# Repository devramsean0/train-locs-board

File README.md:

# train-locs-board
A LED train location board, meant to show the trains on platform at any station

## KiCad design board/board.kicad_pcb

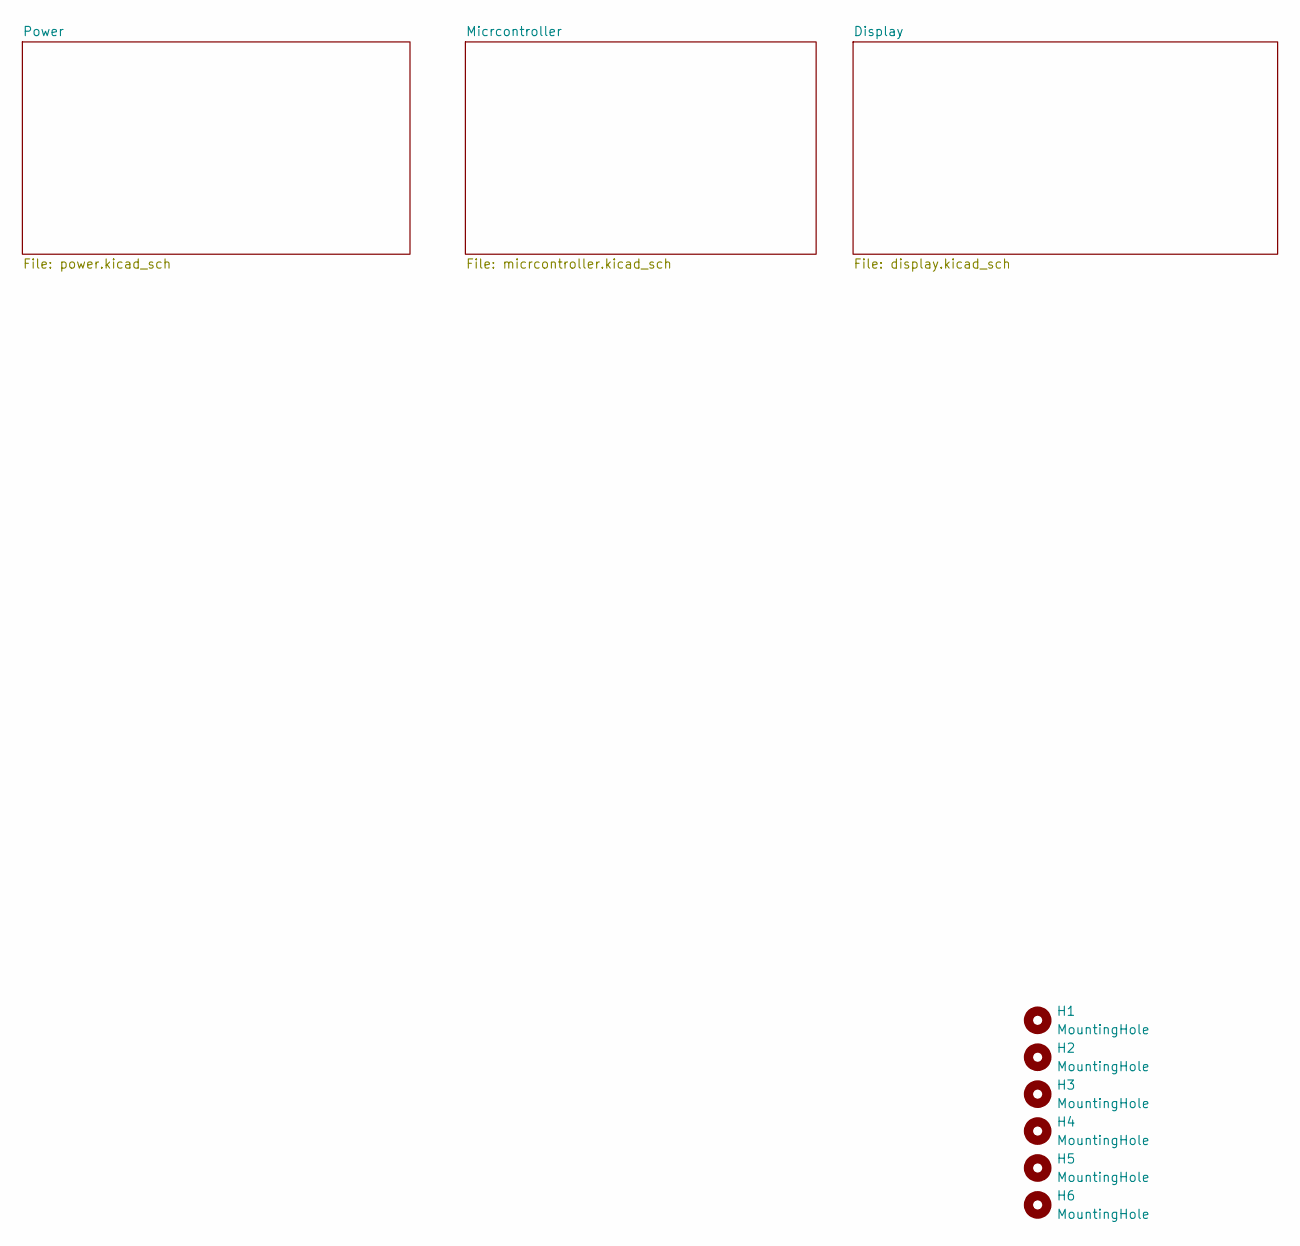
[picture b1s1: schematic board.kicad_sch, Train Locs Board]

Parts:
H1, H2, H3, H4, H5, H6: MountingHole; MountingHole_2.2mm_M2

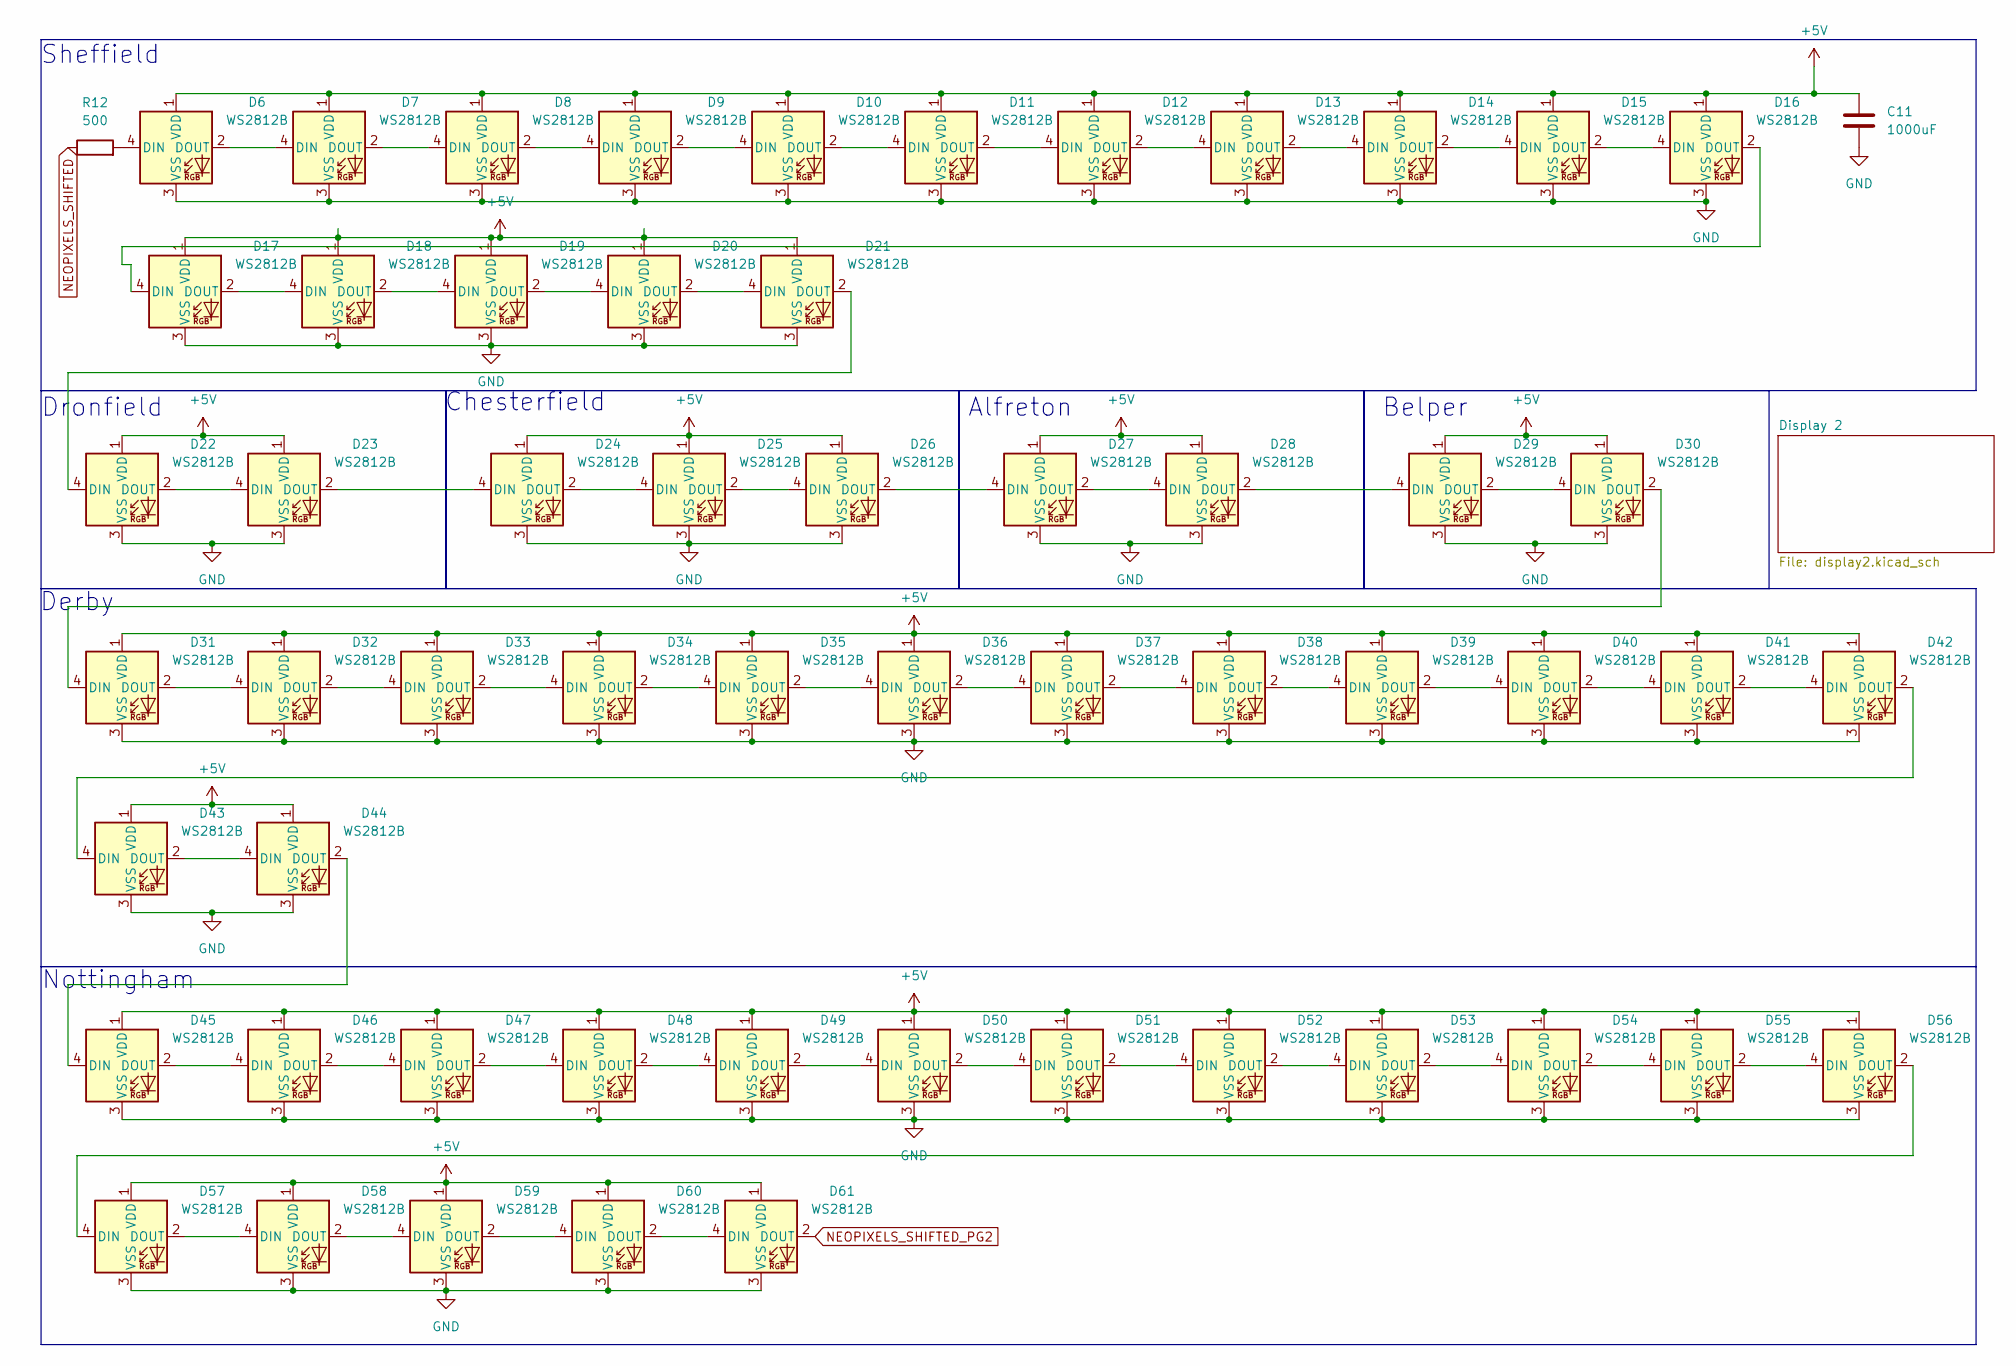
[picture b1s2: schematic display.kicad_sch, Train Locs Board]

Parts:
C11: 1000uF; C_0805_2012Metric
D6, D7, D8, D9, D10, D11, D12, D13, D14, D15, D16, D17, D18, D19, D20, D21, D22, D23, D24, D25, D26, D27, D28, D29, D30, D31, D32, D33, D34, D35, D36, D37, D38, D39, D40, D41, D42, D43, D44, D45, D46, D47, D48, D49, D50, D51, D52, D53, D54, D55, D56, D57, D58, D59, D60, D61: WS2812B; LED_WS2812B_PLCC4_5.0x5.0mm_P3.2mm
R12: 500; R_0805_2012Metric

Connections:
+5V: C11.1, D6.1 (VDD), D7.1 (VDD), D8.1 (VDD), D9.1 (VDD), D10.1 (VDD), D11.1 (VDD), D12.1 (VDD), D13.1 (VDD), D14.1 (VDD), D15.1 (VDD), D16.1 (VDD), D17.1 (VDD), D18.1 (VDD), D19.1 (VDD), D20.1 (VDD), D21.1 (VDD), D22.1 (VDD), D23.1 (VDD), D24.1 (VDD), D25.1 (VDD), D26.1 (VDD), D27.1 (VDD), D28.1 (VDD), D29.1 (VDD), D30.1 (VDD), D31.1 (VDD), D32.1 (VDD), D33.1 (VDD), D34.1 (VDD), D35.1 (VDD), D36.1 (VDD), D37.1 (VDD), D38.1 (VDD), D39.1 (VDD), D40.1 (VDD), D41.1 (VDD), D42.1 (VDD), D43.1 (VDD), D44.1 (VDD), D45.1 (VDD), D46.1 (VDD), D47.1 (VDD), D48.1 (VDD), D49.1 (VDD), D50.1 (VDD), D51.1 (VDD), D52.1 (VDD), D53.1 (VDD), D54.1 (VDD), D55.1 (VDD), D56.1 (VDD), D57.1 (VDD), D58.1 (VDD), D59.1 (VDD), D60.1 (VDD), D61.1 (VDD); also elsewhere on the board
GND: C11.2, D6.3 (VSS), D7.3 (VSS), D8.3 (VSS), D9.3 (VSS), D10.3 (VSS), D11.3 (VSS), D12.3 (VSS), D13.3 (VSS), D14.3 (VSS), D15.3 (VSS), D16.3 (VSS), D17.3 (VSS), D18.3 (VSS), D19.3 (VSS), D20.3 (VSS), D21.3 (VSS), D22.3 (VSS), D23.3 (VSS), D24.3 (VSS), D25.3 (VSS), D26.3 (VSS), D27.3 (VSS), D28.3 (VSS), D29.3 (VSS), D30.3 (VSS), D31.3 (VSS), D32.3 (VSS), D33.3 (VSS), D34.3 (VSS), D35.3 (VSS), D36.3 (VSS), D37.3 (VSS), D38.3 (VSS), D39.3 (VSS), D40.3 (VSS), D41.3 (VSS), D42.3 (VSS), D43.3 (VSS), D44.3 (VSS), D45.3 (VSS), D46.3 (VSS), D47.3 (VSS), D48.3 (VSS), D49.3 (VSS), D50.3 (VSS), D51.3 (VSS), D52.3 (VSS), D53.3 (VSS), D54.3 (VSS), D55.3 (VSS), D56.3 (VSS), D57.3 (VSS), D58.3 (VSS), D59.3 (VSS), D60.3 (VSS), D61.3 (VSS); also elsewhere on the board
NEOPIXELS_SHIFTED: R12.1; also elsewhere on the board
NEOPIXELS_SHIFTED_PG2: D61.2 (DOUT); also elsewhere on the board
unnamed: D6.4 (DIN), R12.2
unnamed: D6.2 (DOUT), D7.4 (DIN)
unnamed: D7.2 (DOUT), D8.4 (DIN)
unnamed: D8.2 (DOUT), D9.4 (DIN)
unnamed: D9.2 (DOUT), D10.4 (DIN)
unnamed: D10.2 (DOUT), D11.4 (DIN)
unnamed: D11.2 (DOUT), D12.4 (DIN)
unnamed: D12.2 (DOUT), D13.4 (DIN)
unnamed: D13.2 (DOUT), D14.4 (DIN)
unnamed: D14.2 (DOUT), D15.4 (DIN)
unnamed: D15.2 (DOUT), D16.4 (DIN)
unnamed: D16.2 (DOUT), D17.4 (DIN)
unnamed: D17.2 (DOUT), D18.4 (DIN)
unnamed: D18.2 (DOUT), D19.4 (DIN)
unnamed: D19.2 (DOUT), D20.4 (DIN)
unnamed: D20.2 (DOUT), D21.4 (DIN)
unnamed: D21.2 (DOUT), D22.4 (DIN)
unnamed: D22.2 (DOUT), D23.4 (DIN)
unnamed: D23.2 (DOUT), D24.4 (DIN)
unnamed: D24.2 (DOUT), D25.4 (DIN)
unnamed: D25.2 (DOUT), D26.4 (DIN)
unnamed: D26.2 (DOUT), D27.4 (DIN)
unnamed: D27.2 (DOUT), D28.4 (DIN)
unnamed: D28.2 (DOUT), D29.4 (DIN)
unnamed: D29.2 (DOUT), D30.4 (DIN)
unnamed: D30.2 (DOUT), D31.4 (DIN)
unnamed: D31.2 (DOUT), D32.4 (DIN)
unnamed: D32.2 (DOUT), D33.4 (DIN)
unnamed: D33.2 (DOUT), D34.4 (DIN)
unnamed: D34.2 (DOUT), D35.4 (DIN)
unnamed: D35.2 (DOUT), D36.4 (DIN)
unnamed: D36.2 (DOUT), D37.4 (DIN)
unnamed: D37.2 (DOUT), D38.4 (DIN)
unnamed: D38.2 (DOUT), D39.4 (DIN)
unnamed: D39.2 (DOUT), D40.4 (DIN)
unnamed: D40.2 (DOUT), D41.4 (DIN)
unnamed: D41.2 (DOUT), D42.4 (DIN)
unnamed: D42.2 (DOUT), D43.4 (DIN)
unnamed: D43.2 (DOUT), D44.4 (DIN)
unnamed: D44.2 (DOUT), D45.4 (DIN)
unnamed: D45.2 (DOUT), D46.4 (DIN)
unnamed: D46.2 (DOUT), D47.4 (DIN)
unnamed: D47.2 (DOUT), D48.4 (DIN)
unnamed: D48.2 (DOUT), D49.4 (DIN)
unnamed: D49.2 (DOUT), D50.4 (DIN)
unnamed: D50.2 (DOUT), D51.4 (DIN)
unnamed: D51.2 (DOUT), D52.4 (DIN)
unnamed: D52.2 (DOUT), D53.4 (DIN)
unnamed: D53.2 (DOUT), D54.4 (DIN)
unnamed: D54.2 (DOUT), D55.4 (DIN)
unnamed: D55.2 (DOUT), D56.4 (DIN)
unnamed: D56.2 (DOUT), D57.4 (DIN)
unnamed: D57.2 (DOUT), D58.4 (DIN)
unnamed: D58.2 (DOUT), D59.4 (DIN)
unnamed: D59.2 (DOUT), D60.4 (DIN)
unnamed: D60.2 (DOUT), D61.4 (DIN)

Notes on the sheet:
Alfreton
Dronfield
Chesterfield
Nottingham
Sheffield
Derby
Belper

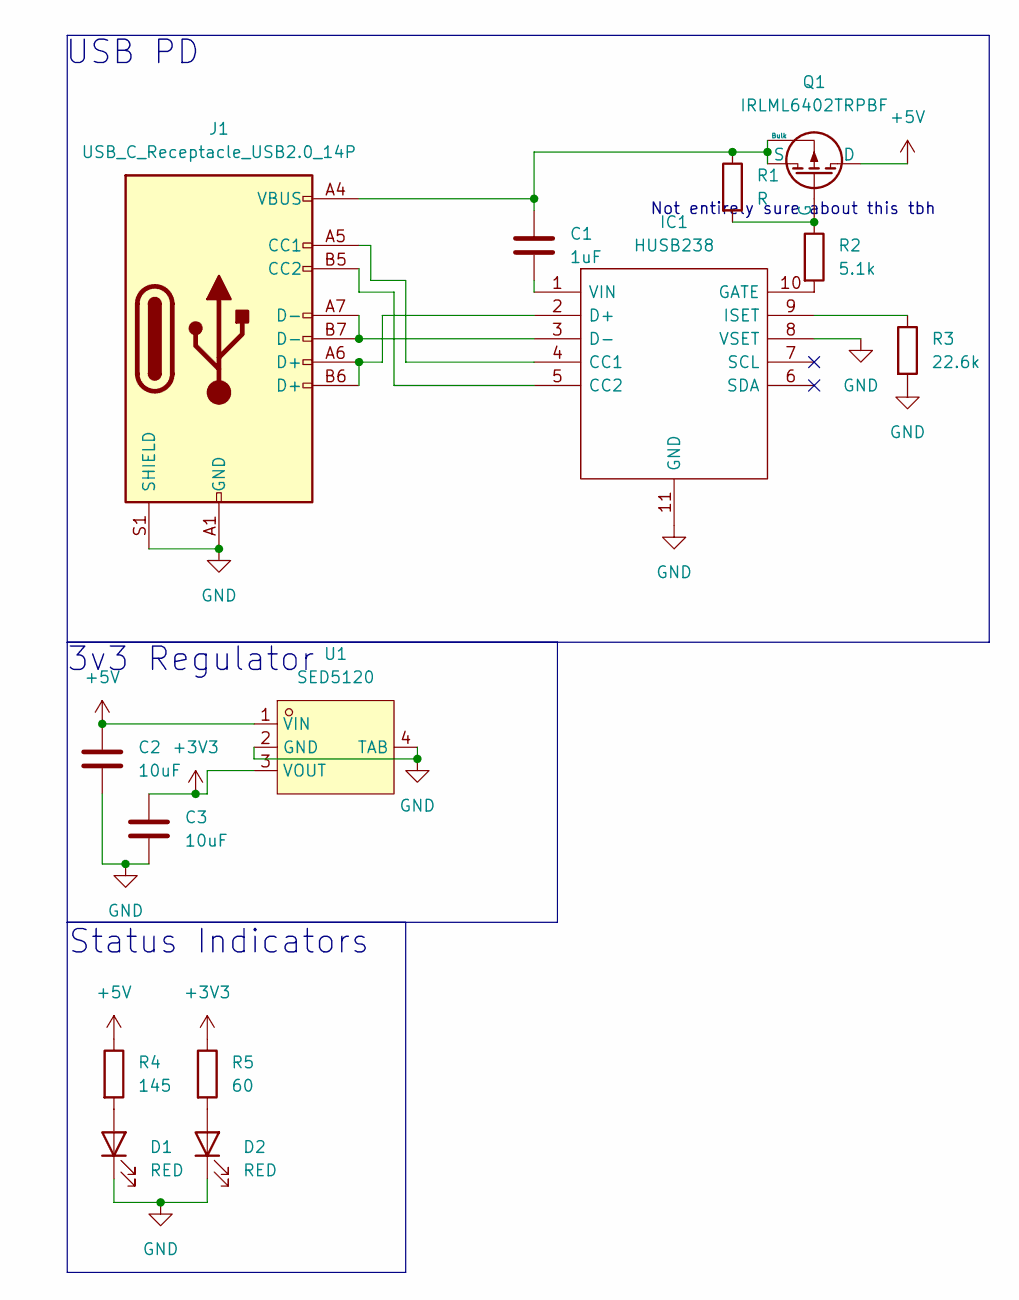
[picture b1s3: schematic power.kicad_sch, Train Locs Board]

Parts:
C1: 1uF; C_0805_2012Metric
C2, C3: 10uF; C_0805_2012Metric
D1, D2: RED; LED_0805_2012Metric
IC1: HUSB238; SON50P300X300X80-11N-D; Manufacturer_Part_Number HUSB238
J1: USB_C_Receptacle_USB2.0_14P; USB_C_Receptacle_G-Switch_GT-USB-7010ASV; LCSC Part C2988369
Q1: IRLML6402TRPBF; SOT-23-3_L2.9-W1.6-P1.90-LS2.8-BR
R1: R; R_0805_2012Metric
R2: 5.1k; R_0805_2012Metric
R3: 22.6k; R_0805_2012Metric
R4: 145; R_0805_2012Metric
R5: 60; R_0805_2012Metric
U1: SED5120; SOT-223-3_L6.5-W3.4-P2.30-LS7.0-BR; LCSC Part C2838439

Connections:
+3V3: C3.1, R5.1, U1.3 (VOUT); also elsewhere on the board
+5V: C2.1, Q1.1 (D), R4.1, U1.1 (VIN); also elsewhere on the board
GND: C2.2, C3.2, D1.1 (K), D2.1 (K), IC1.8 (VSET), IC1.11 (GND), J1.A1 (GND), J1.A12 (GND), J1.B1 (GND), J1.B12 (GND), J1.S1 (SHIELD), R3.2, U1.2 (GND), U1.4 (TAB); also elsewhere on the board
unnamed 13: D1.2 (A), R4.2; also elsewhere on the board
unnamed 14: D2.2 (A), R5.2; also elsewhere on the board
unnamed: IC1.4 (CC1), J1.A5 (CC1)
unnamed: IC1.5 (CC2), J1.B5 (CC2)
unnamed: IC1.2 (D+), J1.A6 (D+), J1.B6 (D+)
unnamed: IC1.3 (D-), J1.A7 (D-), J1.B7 (D-)
unnamed: IC1.10 (GATE), R2.2
unnamed: IC1.9 (ISET), R3.1
unnamed: C1.2, IC1.1 (VIN)
unnamed: C1.1, J1.A4 (VBUS), J1.A9 (VBUS), J1.B4 (VBUS), J1.B9 (VBUS), Q1.3 (S), Q1.4 (Bulk), R1.1
unnamed: Q1.2 (G), R1.2, R2.1

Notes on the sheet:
Status Indicators
Not entirely sure about this tbh
USB PD
3v3 Regulator

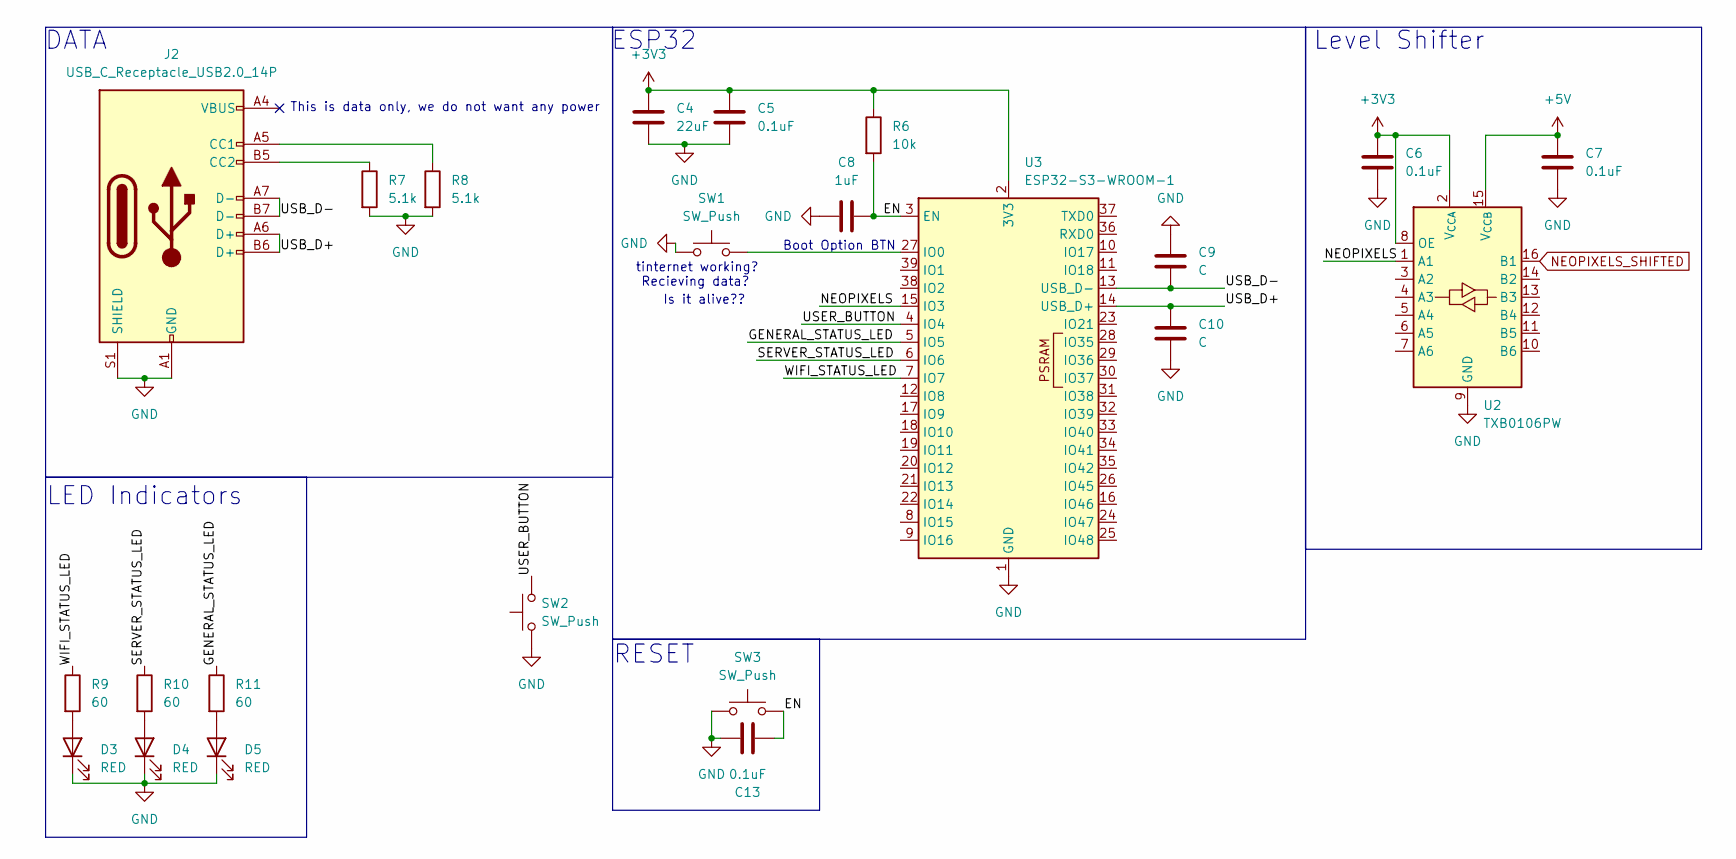
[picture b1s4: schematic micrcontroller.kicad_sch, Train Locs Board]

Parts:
C4: 22uF; C_0805_2012Metric
C5, C6, C7, C13: 0.1uF; C_0805_2012Metric
C8: 1uF; C_0805_2012Metric
C9, C10: C; C_0805_2012Metric
D3, D4, D5: RED; LED_0805_2012Metric
J2: USB_C_Receptacle_USB2.0_14P; USB_C_Receptacle_G-Switch_GT-USB-7010ASV; LCSC Part C2988369
R6: 10k; R_0805_2012Metric
R7, R8: 5.1k; R_0805_2012Metric
R9, R10, R11: 60; R_0805_2012Metric
SW1, SW2, SW3: SW_Push; SW-SMD_4P-L4.2-W3.3-P2.15-LS5.1
U2: TXB0106PW; TSSOP-16_4.4x5mm_P0.65mm
U3: ESP32-S3-WROOM-1

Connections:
+3V3: C4.1, C5.1, C6.1, R6.1, U2.2 (V_{CCA}), U2.8 (OE), U3.2 (3V3); also elsewhere on the board
+5V: C7.1, U2.15 (V_{CCB}); also elsewhere on the board
/Micrcontroller/EN: C8.1, C13.2, R6.2, SW3.2, U3.3 (EN)
/Micrcontroller/GENERAL_STATUS_LED: R11.1, U3.5 (IO5)
/Micrcontroller/NEOPIXELS: U2.1 (A1), U3.15 (IO3)
/Micrcontroller/SERVER_STATUS_LED: R10.1, U3.6 (IO6)
/Micrcontroller/USB_D+: C10.1, J2.A6 (D+), J2.B6 (D+), U3.14 (USB_D+)
/Micrcontroller/USB_D-: C9.2, J2.A7 (D-), J2.B7 (D-), U3.13 (USB_D-)
/Micrcontroller/USER_BUTTON: SW2.2, U3.4 (IO4)
/Micrcontroller/WIFI_STATUS_LED: R9.1, U3.7 (IO7)
GND: C4.2, C5.2, C6.2, C7.2, C8.2, C9.1, C10.2, C13.1, D3.1 (K), D4.1 (K), D5.1 (K), J2.A1 (GND), J2.A12 (GND), J2.B1 (GND), J2.B12 (GND), J2.S1 (SHIELD), R7.2, R8.2, SW1.1, SW2.1, SW3.1, U2.9 (GND), U3.1 (GND), U3.40 (GND), U3.41 (GND); also elsewhere on the board
NEOPIXELS_SHIFTED: U2.16 (B1); also elsewhere on the board
unnamed 15: D3.2 (A), R9.2; also elsewhere on the board
unnamed 16: D4.2 (A), R10.2; also elsewhere on the board
unnamed 17: D5.2 (A), R11.2; also elsewhere on the board
unnamed: J2.A5 (CC1), R8.1
unnamed: J2.B5 (CC2), R7.1
unnamed: SW1.2, U3.27 (IO0)

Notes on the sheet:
RESET
Boot Option BTN
This is data only, we do not want any power
Level Shifter
Recieving data?
tinternet working?
DATA
Is it alive??
LED Indicators
ESP32

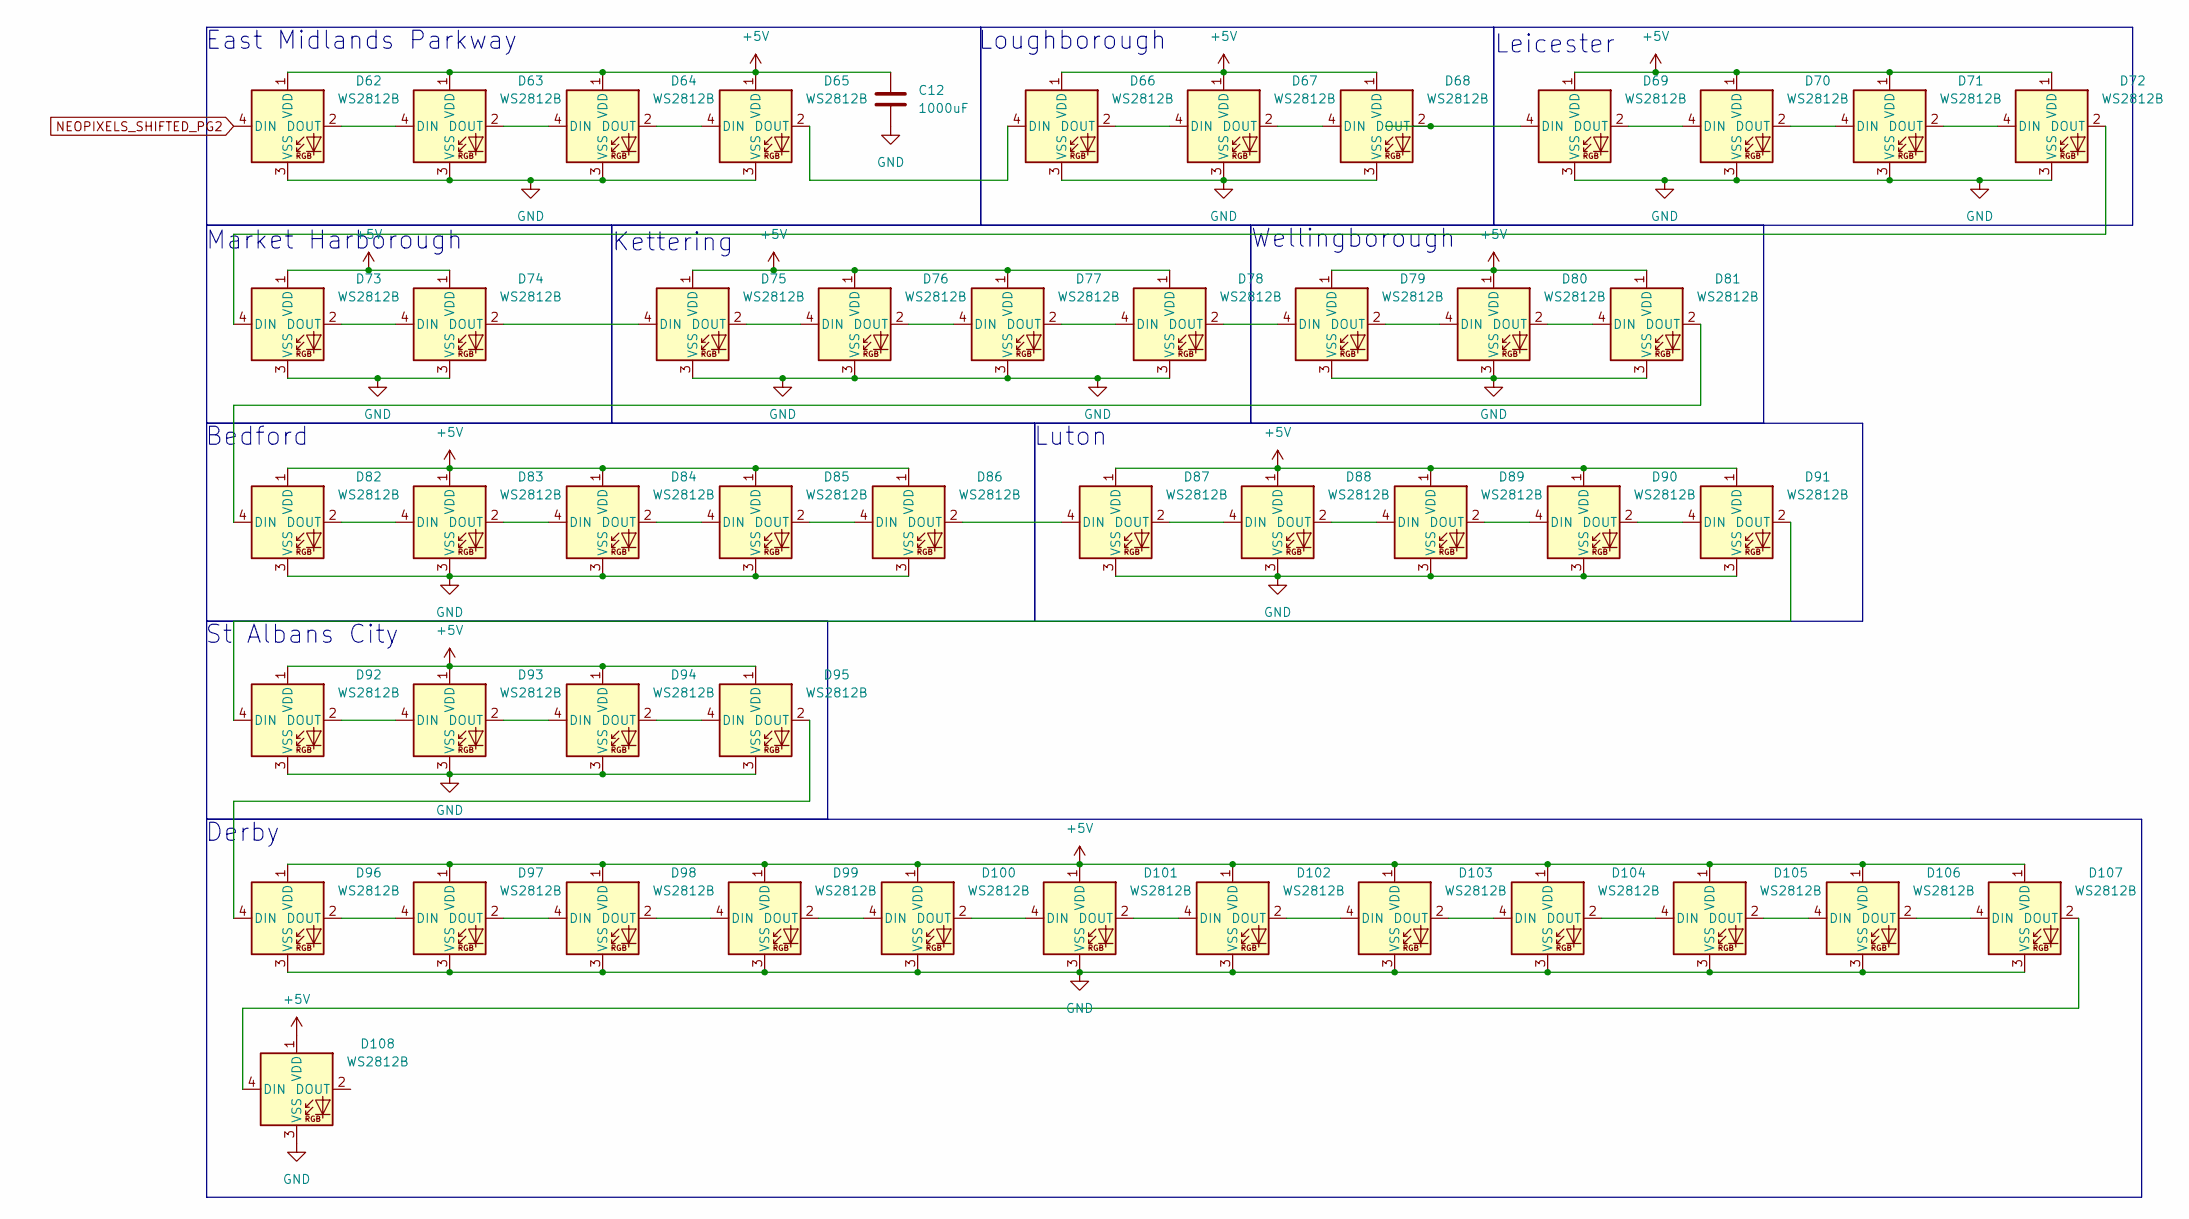
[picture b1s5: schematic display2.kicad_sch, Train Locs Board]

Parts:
C12: 1000uF; C_0805_2012Metric
D62, D63, D64, D65, D66, D67, D68, D69, D70, D71, D72, D73, D74, D75, D76, D77, D78, D79, D80, D81, D82, D83, D84, D85, D86, D87, D88, D89, D90, D91, D92, D93, D94, D95, D96, D97, D98, D99, D100, D101, D102, D103, D104, D105, D106, D107, D108: WS2812B; LED_WS2812B_PLCC4_5.0x5.0mm_P3.2mm

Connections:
+5V: C12.1, D62.1 (VDD), D63.1 (VDD), D64.1 (VDD), D65.1 (VDD), D66.1 (VDD), D67.1 (VDD), D68.1 (VDD), D69.1 (VDD), D70.1 (VDD), D71.1 (VDD), D72.1 (VDD), D73.1 (VDD), D74.1 (VDD), D75.1 (VDD), D76.1 (VDD), D77.1 (VDD), D78.1 (VDD), D79.1 (VDD), D80.1 (VDD), D81.1 (VDD), D82.1 (VDD), D83.1 (VDD), D84.1 (VDD), D85.1 (VDD), D86.1 (VDD), D87.1 (VDD), D88.1 (VDD), D89.1 (VDD), D90.1 (VDD), D91.1 (VDD), D92.1 (VDD), D93.1 (VDD), D94.1 (VDD), D95.1 (VDD), D96.1 (VDD), D97.1 (VDD), D98.1 (VDD), D99.1 (VDD), D100.1 (VDD), D101.1 (VDD), D102.1 (VDD), D103.1 (VDD), D104.1 (VDD), D105.1 (VDD), D106.1 (VDD), D107.1 (VDD), D108.1 (VDD); also elsewhere on the board
GND: C12.2, D62.3 (VSS), D63.3 (VSS), D64.3 (VSS), D65.3 (VSS), D66.3 (VSS), D67.3 (VSS), D68.3 (VSS), D69.3 (VSS), D70.3 (VSS), D71.3 (VSS), D72.3 (VSS), D73.3 (VSS), D74.3 (VSS), D75.3 (VSS), D76.3 (VSS), D77.3 (VSS), D78.3 (VSS), D79.3 (VSS), D80.3 (VSS), D81.3 (VSS), D82.3 (VSS), D83.3 (VSS), D84.3 (VSS), D85.3 (VSS), D86.3 (VSS), D87.3 (VSS), D88.3 (VSS), D89.3 (VSS), D90.3 (VSS), D91.3 (VSS), D92.3 (VSS), D93.3 (VSS), D94.3 (VSS), D95.3 (VSS), D96.3 (VSS), D97.3 (VSS), D98.3 (VSS), D99.3 (VSS), D100.3 (VSS), D101.3 (VSS), D102.3 (VSS), D103.3 (VSS), D104.3 (VSS), D105.3 (VSS), D106.3 (VSS), D107.3 (VSS), D108.3 (VSS); also elsewhere on the board
NEOPIXELS_SHIFTED_PG2: D62.4 (DIN); also elsewhere on the board
unnamed: D62.2 (DOUT), D63.4 (DIN)
unnamed: D63.2 (DOUT), D64.4 (DIN)
unnamed: D64.2 (DOUT), D65.4 (DIN)
unnamed: D65.2 (DOUT), D66.4 (DIN)
unnamed: D66.2 (DOUT), D67.4 (DIN)
unnamed: D67.2 (DOUT), D68.4 (DIN)
unnamed: D68.2 (DOUT), D69.4 (DIN)
unnamed: D69.2 (DOUT), D70.4 (DIN)
unnamed: D70.2 (DOUT), D71.4 (DIN)
unnamed: D71.2 (DOUT), D72.4 (DIN)
unnamed: D72.2 (DOUT), D73.4 (DIN)
unnamed: D73.2 (DOUT), D74.4 (DIN)
unnamed: D74.2 (DOUT), D75.4 (DIN)
unnamed: D75.2 (DOUT), D76.4 (DIN)
unnamed: D76.2 (DOUT), D77.4 (DIN)
unnamed: D77.2 (DOUT), D78.4 (DIN)
unnamed: D78.2 (DOUT), D79.4 (DIN)
unnamed: D79.2 (DOUT), D80.4 (DIN)
unnamed: D80.2 (DOUT), D81.4 (DIN)
unnamed: D81.2 (DOUT), D82.4 (DIN)
unnamed: D82.2 (DOUT), D83.4 (DIN)
unnamed: D83.2 (DOUT), D84.4 (DIN)
unnamed: D84.2 (DOUT), D85.4 (DIN)
unnamed: D85.2 (DOUT), D86.4 (DIN)
unnamed: D86.2 (DOUT), D87.4 (DIN)
unnamed: D87.2 (DOUT), D88.4 (DIN)
unnamed: D88.2 (DOUT), D89.4 (DIN)
unnamed: D89.2 (DOUT), D90.4 (DIN)
unnamed: D90.2 (DOUT), D91.4 (DIN)
unnamed: D91.2 (DOUT), D92.4 (DIN)
unnamed: D92.2 (DOUT), D93.4 (DIN)
unnamed: D93.2 (DOUT), D94.4 (DIN)
unnamed: D94.2 (DOUT), D95.4 (DIN)
unnamed: D95.2 (DOUT), D96.4 (DIN)
unnamed: D96.2 (DOUT), D97.4 (DIN)
unnamed: D97.2 (DOUT), D98.4 (DIN)
unnamed: D98.2 (DOUT), D99.4 (DIN)
unnamed: D99.2 (DOUT), D100.4 (DIN)
unnamed: D100.2 (DOUT), D101.4 (DIN)
unnamed: D101.2 (DOUT), D102.4 (DIN)
unnamed: D102.2 (DOUT), D103.4 (DIN)
unnamed: D103.2 (DOUT), D104.4 (DIN)
unnamed: D104.2 (DOUT), D105.4 (DIN)
unnamed: D105.2 (DOUT), D106.4 (DIN)
unnamed: D106.2 (DOUT), D107.4 (DIN)
unnamed: D107.2 (DOUT), D108.4 (DIN)

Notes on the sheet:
Bedford
East Midlands Parkway
Loughborough
Kettering
Luton
St Albans City
Market Harborough
Wellingborough
Leicester
Derby

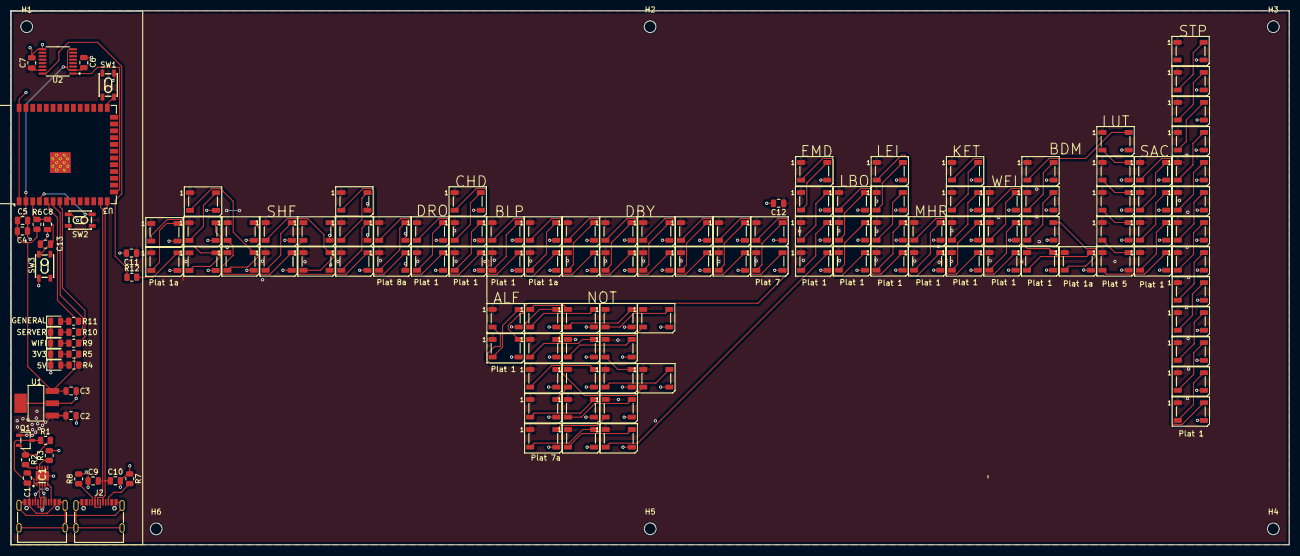
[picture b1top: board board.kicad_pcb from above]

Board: 4 copper layers, 239.4 x 100.0 mm, 149 parts (0 on the bottom side), 132 nets.

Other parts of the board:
3V3, 5V: RED; LED_0805_2012Metric
GENERAL: RED; LED_0805_2012Metric
SERVER: RED; LED_0805_2012Metric
WIFI: RED; LED_0805_2012Metric

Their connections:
GND: 3V3.1 (K), 5V.1 (K), GENERAL.1 (K), SERVER.1 (K), WIFI.1 (K); also elsewhere on the board
unnamed 13: 5V.2 (A); also elsewhere on the board
unnamed 14: 3V3.2 (A); also elsewhere on the board
unnamed 15: WIFI.2 (A); also elsewhere on the board
unnamed 16: SERVER.2 (A); also elsewhere on the board
unnamed 17: GENERAL.2 (A); also elsewhere on the board

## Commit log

2025-06-04 What is this?? A Journal?
2025-06-04 More Journal work
2025-06-04 More Journalling
2025-06-05 Some bits of station info, and fixed image
2025-06-05 Hm, more Journal work :)
2025-06-05 Fix slight mistakes
2025-06-06 We have Power
2025-06-06 The microcontroller
2025-06-06 Display Schematic
2025-06-06 [ImgBot] Optimize images
    *Total -- 711.36kb -> 522.52kb (26.55%)
    /Journal/images/husb238-iset-table.png -- 57.70kb -> 22.13kb (61.64%)
    /Journal/images/husb238-vset-table.png -- 39.56kb -> 15.43kb (60.99%)
    /Journal/images/schematic-microcontroller-v1.png -- 40.86kb -> 19.88kb (51.34%)
    /Journal/images/schematic-power-v1.png -- 27.70kb -> 14.12kb (49.02%)
    /Journal/images/schematic-display-p2-v1.png -- 29.68kb -> 15.16kb (48.92%)
2025-06-06 Lots of silly train things
2025-06-08 Micrcontroller, but wired up
2025-06-08 Lay out some stations
2025-06-15 Finishing touches on the PCB
